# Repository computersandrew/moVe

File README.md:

# moVe

High-performance (ish) STM32H7 sensor suite and navigation platform for autonomous drones, planes, cars, and boats. Featuring ICM-20948, BMP390, u-blox M10 GNSS, u-blox NORA-B261 Bluetooth LE, and an RGB TFT cockpit display path. Will include non-volatile storage for datalogging, map/chart assets, and USB.

PCB Hardware Design and Implementation done using Ki-Cad

3D Design and Modeling done using Siemens NX

Prototyping & Manufacturing done at Rensselaer Polytechnic Institute

To include a header for possible 3.3V LiPo Cells

PCA9306 Level Shifter(s)

This is a plain C STM32 HAL implementation for:

## Custom Board

- Main MCU: STM32H723ZGT6.
- STM32H723ZG datasheet: [STMicroelectronics PDF](https://www.st.com/resource/en/datasheet/stm32h723zg.pdf).
- Designed as a custom single board in KiCad.
- Pinout: `docs/pinout.md`.
- KiCad test platform PCB: `hardware/moVe_test/` (schematic, routed 4-layer board, images).
- u-blox NORA-B261 Bluetooth LE module on a UART host link, with reset/recovery/test lines reserved.
- Display direction: Newhaven `NHD-5.0-800480TF-ATXL-CTP`, driven with LTDC RGB, DMA2D, and external SDRAM.
- Storage direction: `SDMMC2` microSD in 4-bit mode for logs and chart/map tiles.

## Test Platform PCB (KiCad)

A round **4.2 in (106.68 mm), 4-layer** bring-up board that carries every subsystem below lives in
[`hardware/moVe_test/`](hardware/moVe_test/) — full KiCad project, schematic PDF, layer images and design notes.

- **Fully routed:** 521/521 connections, DRC 0 errors, 146 parts.
- **Stackup:** signal / solid GND / +3V3 plane / signal (1.6 mm).
- **Schematic:** 7 sheets (Power, MCU, Memory, Display, Sensors, Radio, CO sensor), each organized into titled functional blocks — [PDF](hardware/moVe_test/moVe_test_schematic.pdf).
- **Pin assignments:** previously TBD pins are now assigned in [`docs/pinout.md`](docs/pinout.md).
- **Cost:** about $142 per board ($77 components + $64 display + PCB), with a priced BOM in [`bom/moVe_test_BOM.csv`](hardware/moVe_test/bom/moVe_test_BOM.csv).

See [`hardware/moVe_test/README.md`](hardware/moVe_test/README.md) for all layers, every schematic sheet, the
stackup rationale, design notes and how to regenerate the files.

## ICM-20948 + Madgwick AHRS for STM32H7
[Datasheet](https://d17t6iyxenbwp1.cloudfront.net/s3fs-public/2026-01/DS-000189-ICM-20948-v1.6.pdf?VersionId=XteIUeEiGGKWJDQjSzr3D2K3OIitFvHY)

- To run on 1.8V Bus - Low-Dropout Regulator (MIC5225)
- ICM-20948 by InvenSense TDK
- ICM-20948 accelerometer and gyroscope over I2C. 
- ICM-20948 contains the AK09916 magnetometer (allegedly according to adafruit) through ICM-20948 bypass mode.
- Madgwick 6-axis or 9-axis attitude filtering.
- Roll, pitch, yaw, and aircraft/drone display ready instrument values.
- Roll/Pitch applications for marine use

## BMP390 + Simple Kalman Filtering for STM32H7
[Datasheet](https://www.mouser.com/datasheet/3/1046/1/bst_bmp390_ds002.pdf)
- To run on 3.3V Bus
- BMP390 by Bosch 
- I2C, SPI capabilities
- Also, temperature capabilities 
- Compensated pressure and temperature over I2C.
- Pressure altitude conversion with configurable sea-level pressure.
- Two-state Kalman filter for altitude and vertical speed.

## U-Blox MAX-M10S for STM32H7

[Datasheet](https://content.u-blox.com/sites/default/files/MAX-M10S_DataSheet_UBX-20035208.pdf)
- To run on 3.3V Bus
- moving map/navigation
- Outputs MSL elevation data, Ground Speed, Lat/Long Coordinates
- Will include uFL connector, as well as ceramic patch antenna by default
- Parses both UBX binary navigation messages and NMEA sentences.
- GPS ground speed feeds the airspeed display as a fallback speed source.

## u-blox NORA-B261 Bluetooth LE Module
[Datasheet](https://content.u-blox.com/sites/default/files/documents/NORA-B26_DataSheet_UBXDOC-465451970-4608.pdf)

- To run on 3.3V bus.
- NORA-B261 uses u-connectXpress firmware with an AT-command host interface.
- Host interface starts as asynchronous UART from STM32H723ZGT6 to NORA-B261.
- Optional RTS/CTS hardware flow control should be reserved in the schematic.
- Include NORA reset, recovery/test access, and optional IRQ/attention GPIOs.
- The B261 variant uses an antenna pin, so route a 50 ohm 2.4 GHz RF path to a chip antenna or u.FL.

## Graphical Display Path
[Datasheet](https://newhavendisplay.com/content/specs/NHD-5.0-800480TF-ATXL-CTP.pdf)

- Newhaven `NHD-5.0-800480TF-ATXL-CTP` 5 inch, 800x480 RGB TFT with capacitive touch.
- STM32 `LTDC` drives the parallel RGB display interface.
- STM32 `DMA2D` accelerates fills, blits, and pixel format conversion.
- External SDRAM on `FMC SDRAM 1` holds the framebuffer; start with a 16-bit SDRAM bus.
- Use `RGB565` for the first framebuffer format even though the physical panel interface is RGB888.
- Touch uses I2C plus touch interrupt/reset GPIOs.
- Backlight needs a separate LED boost/current driver, not a direct STM32 GPIO.
- FAA sectionals/charts should be preprocessed into raster tiles and loaded from SD instead of rendering full PDFs on the MCU.
- Moving-map firmware maps current GNSS position to predownloaded XYZ raster tiles and can stream the current tile state over the NORA-B261 link.
- Google Maps tiles should only be used through a licensed/offline workflow that permits embedded use; the firmware tile math is provider-neutral.

## Aircraft Carbon Monoxide Sensor

- Aircraft-only MQ-7/MQ-7B carbon monoxide sensor direction.
- Firmware exposes alert triggers at 25 ppm, 50 ppm, and 100 ppm.
- MQ-7 heater cycling is modeled as a high-temperature clean phase and low-temperature measurement phase.
- Real CO ppm readings require analog calibration, heater driver hardware, and validation before any aircraft safety use.

## Parts List

- GitHub spreadsheet/BOM: `docs/parts.csv`
- STM32H723ZGT6 MCU
- u-blox NORA-B261 Bluetooth LE module
- U-Blox MAX-M10S GNSS receiver
- ICM-20948 9-axis IMU
- BMP390 pressure/temperature sensor
- Aircraft-only MQ-7/MQ-7B carbon monoxide sensor
- Newhaven `NHD-5.0-800480TF-ATXL-CTP` RGB TFT with capacitive touch
- 16-bit external SDRAM for framebuffer storage
- Backlight LED boost/current driver for the TFT
- PCA9306 level shifter(s), if mixed-voltage I2C is kept
- MIC5225 or equivalent low-noise LDO for 1.8 V rail
- 3.3 V regulator sized for STM32, GNSS, NORA-B261, SD, and display
- USB-C Connector (5V 500mA)
- SD card socket
- Optional battery connector and protected 2-cell input path
- ADC battery-sense divider and optional current-sense amplifier
- GNSS antenna path: u.FL and/or ceramic patch antenna
- NORA-B261 antenna path: chip antenna or u.FL with matching network
- STM32 SWD header
- NORA-B261 reset/recovery test pads
- Reset and boot buttons or test pads

## Files (so far) will update

- `Core/Inc/icm20948.h`
- `Core/Src/icm20948.c`
- `Core/Inc/madgwick.h`
- `Core/Src/madgwick.c`
- `Core/Inc/icm20948_madgwick_example.h`
- `Core/Src/icm20948_madgwick_example.c`
- `Core/Inc/navigation_fusion.h`
- `Core/Src/navigation_fusion.c`
- `Core/Inc/moving_map.h`
- `Core/Src/moving_map.c`
- `Core/Inc/nora_b261.h`
- `Core/Src/nora_b261.c`
- `Core/Src/main.c`
- `moVe.ioc`
- `docs/pinout.md`
- `docs/parts.csv`
- `Core/Inc/bmp390.h`
- `Core/Src/bmp390.c`
- `Core/Inc/kalman_altitude.h`
- `Core/Src/kalman_altitude.c`
- `Core/Inc/max_m10s.h`
- `Core/Src/max_m10s.c`
- `Aircraft/Inc/aircraft_instruments.h`
- `Aircraft/Src/aircraft_instruments.c`
- `Aircraft/Inc/attitude_indicator.h`
- `Aircraft/Src/attitude_indicator.c`
- `Aircraft/Inc/turn_slip.h`
- `Aircraft/Src/turn_slip.c`
- `Aircraft/Inc/heading_indicator.h`
- `Aircraft/Src/heading_indicator.c`
- `Aircraft/Inc/altimeter.h`
- `Aircraft/Src/altimeter.c`
- `Aircraft/Inc/airspeed_indicator.h`
- `Aircraft/Src/airspeed_indicator.c`
- `Aircraft/Inc/g_meter.h`
- `Aircraft/Src/g_meter.c`
- `Aircraft/Inc/mq7_co.h`
- `Aircraft/Src/mq7_co.c`
- `Aircraft/Inc/vertical_speed_indicator.h`
- `Aircraft/Src/vertical_speed_indicator.c`
- `Aircraft/Inc/aircraft_math.h`
- `Aircraft/Src/aircraft_math.c`
- `Crew/Inc/crew_instruments.h`
- `Crew/Src/crew_instruments.c`

## Aircraft Display Outputs

- Converts the same IMU, GPS, and BMP390 data path into aircraft-facing instrument values.
- Attitude reports roll and pitch from filtered AHRS output.
- Turn-and-slip reports yaw-rate turn indication and lateral-acceleration slip ball.
- Heading reports display heading with configurable magnetic declination.
- Altimeter and VSI report altitude and vertical speed from BMP390 pressure and the altitude filter.
- Airspeed reports estimated true airspeed from GNSS speed plus pressure/temperature, with GPS ground-speed fallback.
- G-meter reports smoothed normal acceleration plus positive and negative peak G values.

## Crew Display Outputs

- Converts the same IMU, GPS, and BMP390 data path into rowing-facing values.
- Roll state reports `Port`, `Starboard`, or `Set` from filtered roll angle.
- Speed uses GNSS ground speed when valid and exposes meters/second, km/h, and knots.
- Stroke rate estimates strokes per minute from cyclic IMU acceleration.
- Stroke phase reports `Catch`, `Drive`, or `Recovery` with phase and cycle timing.
- Temperature comes from the BMP390 compensated temperature sample.

## STM32CubeIDE Use

Copy the `Core/Inc`, `Core/Src`, `Aircraft/Inc`, `Aircraft/Src`, `Crew/Inc`, and `Crew/Src` files into your STM32H7 project. Enable I2C in CubeMX, then make sure the example uses the matching handle:

```c
extern I2C_HandleTypeDef hi2c1;
```

The Cube-style entry point is `Core/Src/main.c`. It shows the expected HAL init order for the H723 board direction, including I2C sensors, GPS UART, NORA-B261 UART, ADC battery sense, CRC, FMC SDRAM, DMA2D, LTDC, SDMMC2, USB OTG HS device mode with internal FS PHY, GPS UART byte reception, and the navigation fusion update loop.

Legacy compatibility wrappers are still available. Call this once after `MX_I2C1_Init()`:

```c
Attitude_Init();
```

Call this repeatedly from your main loop or a fixed-rate task:

```c
Attitude_Update();
```

The latest Euler angles are in:

```c
#include "icm20948_madgwick_example.h"

attitude_deg.roll_deg;
attitude_deg.pitch_deg;
attitude_deg.yaw_deg;
```

The moving-map tile state is in:

```c
#include "navigation_fusion.h"

const MovingMapState *map_state =
    NavigationFusion_GetMovingMapState(&navigation_fusion);

char nora_frame[160];
NavigationFusion_BuildNoraB261MovingMapFrame(&navigation_fusion,
                                             "maps/faa",
                                             "tile",
                                             nora_frame,
                                             sizeof(nora_frame));
```

The display-ready aircraft instrument values are in:

```c
#include "icm20948_madgwick_example.h"

aircraft_display->attitude.roll_deg;
aircraft_display->attitude.pitch_deg;
aircraft_display->turn_slip.turn_rate_deg_s;
aircraft_display->turn_slip.standard_rate_fraction;
aircraft_display->turn_slip.slip_ball;
aircraft_display->heading.display_heading_deg;
aircraft_display->altimeter.display_altitude_ft;
aircraft_display->vsi.vertical_speed_fpm;
aircraft_display->airspeed.display_true_airspeed_kt;
aircraft_display->g_meter.normal_g;
aircraft_display->g_meter.peak_positive_g;
aircraft_display->g_meter.peak_negative_g;
AircraftInstruments_ResetGMeterPeaks(&aircraft_instruments);
```

The crew display values are in:

```c
#include "icm20948_madgwick_example.h"

crew_display->roll_deg;
CrewInstruments_RollStateText(crew_display->roll_state);
crew_display->speed_mps;
crew_display->speed_kph;
crew_display->speed_kt;
crew_display->strokes_per_minute;
CrewInstruments_StrokePhaseText(crew_display->stroke_phase);
crew_display->current_phase_time_s;
crew_display->catch_time_s;
crew_display->drive_time_s;
crew_display->recovery_time_s;
crew_display->drive_recovery_ratio;
crew_display->recovery_drive_ratio;
crew_display->stroke_cycle_time_s;
crew_display->temperature_c;
```

The aircraft display layer is split by instrument. `Aircraft/Src/aircraft_instruments.c` coordinates the attitude indicator, turn-and-slip, heading card, altimeter, VSI, and airspeed modules without owning their display math.
The crew display layer is in `Crew/Src/crew_instruments.c` and is updated by `NavigationFusion_Update()` alongside the aircraft outputs.

## Notes

- Gyro values are converted from degrees/second to radians/second before entering Madgwick.
- The driver configures accel at +/-16 g and gyro at +/-2000 dps.
- The magnetometer is read at 100 Hz. If no new magnetometer data is ready, the filter falls back to the IMU-only Madgwick update for that frame.
- Real yaw quality depends heavily on magnetometer hard-iron and soft-iron calibration. Use `ICM20948_SetMagCalibration()` after you measure your board's calibration values.
- If yaw moves the wrong way, align the AK09916 axes to the accel/gyro frame with `ICM20948_SetMagAxisTransform()`.
- Set local magnetic declination with `AircraftInstruments_SetDeclination()` if the heading display should show true heading instead of magnetic heading.
- Set local altimeter pressure with `BMP390_SetSeaLevelPressure()` before converting pressure to altitude.
- The airspeed indicator displays estimated true airspeed when it has GPS speed plus BMP390 static pressure and temperature. If temperature or pressure are unavailable, it falls back to pressure-altitude ISA correction, then GPS ground speed.
- Aircraft use needs independent validation, redundancy, failure annunciation, and compliance work before it can be trusted as flight-critical instrumentation.
- If AD0 is high on your board, initialize with `ICM20948_ADDR_AD0_HIGH` instead of `ICM20948_ADDR_AD0_LOW`.
- Link with the math library if your toolchain requires it, usually by adding `-lm`.

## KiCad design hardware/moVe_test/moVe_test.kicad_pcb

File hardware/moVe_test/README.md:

# moVe test platform — KiCad hardware (rev A)

A round **4.2 in (106.68 mm)**, **4-layer** bring-up board for the moVe STM32H723ZGT6 platform. It carries every
subsystem from the main README: SDRAM framebuffer, RGB TFT + capacitive touch, microSD, ICM-20948, BMP390,
MAX-M10S GNSS, NORA-B261 Bluetooth LE, the aircraft MQ-7 CO sensor, USB-C and a 2S battery input.

* Schematic: [`moVe_test_schematic.pdf`](moVe_test_schematic.pdf) (8 pages) · KiCad project: [`moVe_test.kicad_pro`](moVe_test.kicad_pro)
* Status: **fully routed — 521/521 connections, DRC 0 errors, 0 unconnected**, 146 parts
* Format: KiCad 7 (KiCad 8/9 open it and offer to upgrade)

<p align="center"><em>Top side (left) and bottom side, mirrored (right).</em></p>

---

## Layer stackup — 4 layers

| Layer | Use |
|---|---|
| L1 `F.Cu` | Signals + components, GND pour |
| L2 `In1.Cu` | Solid GND plane |
| L3 `In2.Cu` | Solid +3V3 plane |
| L4 `B.Cu` | Signals + MCU/SDRAM decoupling, GND pour |

1.6 mm board (e.g. JLC04161H-7628). Rules: 0.15 mm track / 0.127 mm clearance, 0.6/0.3 mm vias, power 0.5 mm,
RF 0.36 mm (≈50 Ω microstrip over L2 with 7628 prepreg — confirm with your fab's impedance calculator).

**Why 4 layers:** 2 layers can't give the ~100 MHz SDRAM bus, the 24-bit LTDC bus, USB and the two 50 Ω RF feeds an
unbroken reference plane. The routed result confirms 4 is enough: every signal fits on L1/L4 with L2/L3 left as
solid planes (521 connections, 498 vias, ~7.1 m of copper). 6 layers is the upgrade path only if you want the SDRAM
bus length-matched on an inner stripline layer.

<table>
  <tr>
    <td></td>
    <td></td>
  </tr>
  <tr>
    <td></td>
    <td></td>
  </tr>
  <tr>
    <td></td>
    <td></td>
  </tr>
</table>

Both copper layers together (red = top, blue = bottom):

---

## Schematic

Each sheet is organized into titled functional blocks: supply arrows point up and GND down, same-net power
pins are bussed, net names sit on wires for sheet-local nets, and global flag labels mark nets shared between
sheets. Text placement is collision-checked, so no text overlaps.

| Sheet | Blocks |
|---|---|
| [Power](images/sch_2_power.png) | USB-C input, power path (USB / 2S battery), 3.3 V and 1.8 V regulators, voltage sense, power LED, test points, mounting holes |
| [MCU](images/sch_3_mcu.png) | STM32H723ZGT6, supply decoupling, 25 MHz / 32.768 kHz clocks, reset and boot, SWD, status LEDs, expansion header |
| [Memory](images/sch_4_memory.png) | SDRAM framebuffer, microSD (SDMMC2) |
| [Display](images/sch_5_display.png) | 40-pin RGB TFT connector, capacitive touch, TPS61165 backlight driver |
| [Sensors](images/sch_6_sensors.png) | ICM-20948 (1.8 V), BMP390, PCA9306 I2C level shift, IMU INT level shift |
| [Radio](images/sch_7_radio.png) | MAX-M10S GNSS, NORA-B261 Bluetooth LE |
| [CO sensor](images/sch_8_co_sensor.png) | MQ-7 heater and sense (aircraft build) |

<details open><summary><b>Power</b></summary></details>
<details><summary><b>MCU</b></summary></details>
<details><summary><b>Memory</b></summary></details>
<details><summary><b>Display</b></summary></details>
<details><summary><b>Sensors</b></summary></details>
<details><summary><b>Radio</b></summary></details>
<details><summary><b>CO sensor</b></summary></details>

For full resolution open the [PDF](moVe_test_schematic.pdf) or the project in KiCad.

---

## Pin assignments added for this board

These were TBD in [`docs/pinout.md`](../../docs/pinout.md) (now updated). Mirror them in `moVe.ioc` (CubeMX) before
generating firmware.

| Signal | STM32 pin | Notes |
|---|---|---|
| BLE_CTS / BLE_RTS | PD11 / PD12 | USART3 CTS/RTS (AF7). MCU RTS → NORA CTS (F9), NORA RTS (F8) → MCU CTS |
| BLE_RESET_N, BLE_SW1, BLE_SW2 | PD13, PD4, PD5 | NORA J3, D8, C8 |
| BLE_WAKE | PC12 | NORA J9; shared with expansion header pin 7 |
| GPS_RESET_N, GPS_EXTINT, GPS_TIMEPULSE | PG3, PG14, PE2 | TIMEPULSE on EXTI2 |
| IMU_INT, BARO_INT, TOUCH_INT_N, SD_DETECT | PE3, PB4, PC13, PC8 | separate EXTI lines 3 / 4 / 13 / 8 |
| TOUCH_RST_N, LCD_STBYB | PB12, PB13 | STBYB has a 10k pull-down (panel in standby until firmware enables it) |
| BL_PWM, MQ7_HEAT | PB8 (TIM16_CH1), PB9 (TIM17_CH1) | independent timers |
| MQ7_ADC, VBAT_SENSE, VBUS_SENSE | PC5 (ADC12_INP8), PC4, PA9 | VBUS 10k/20k; VBAT 100k/33k (8.4 V → 2.08 V) |
| LED1, LED2 | PF6, PF7 | |
| SWO | PB3 | 10-pin Cortex SWD header |
| Expansion header J2 | — | 3V3, GND, SCL, SDA, PF8, PF9, PC12/BLE_WAKE, VSYS |

PD7 and PB2 are left unused.

## Bill of materials and cost

Full BOM with quantities, MPNs, unit prices and DigiKey links: [`bom/moVe_test_BOM.csv`](bom/moVe_test_BOM.csv) (61 lines, 130 fitted parts).

| | Per board (USD) |
|---|---|
| Components (excluding display) | $76.57 |
| Display — NHD-5.0-800480TF-ATXL-CTP (off-board) | $63.83 |
| PCB fabrication, 4-layer (estimate) | $2.00 |
| **Total** | **$142.40** |

About $712 for a 5-board build. Prices are quantity-1, USD, without shipping or tariffs, as of Nov 2026.

* Most ICs and connectors come from the April 2026 prices in [`docs/parts.csv`](../../docs/parts.csv); the rest are distributor prices from Nov 2026 (the source is in the `Price basis` column).
* Passives, LEDs, the small MOSFETs and diodes, and the 1x8 header are estimates assuming 10+ cut-tape quantities. At single-piece prices (~$0.10 each) they add about $8 per board.
* For the generic passives, the link is a DigiKey search by value and package; choose a specific part before ordering.
* PCB cost is a placeholder; get a real quote by uploading the Gerbers.
* The display spec calls out a Molex FPC connector; J6 is a Hirose FH12-40S. Check the contact side before ordering.

## Design notes worth checking

* **Power:** USB-C VBUS → 1.1 A PTC → `+5V` (MQ-7 heater) → SS34 → `VSYS`; 2S battery (JST-PH) → SS34 → `VSYS`.
  VSYS → TLV1117-33 → +3V3 → AP2112K-1.8 → +1V8. At 8.4 V battery input the TLV1117 dissipates ~1.5 W; consider a buck converter for battery use.
* **MCU:** 25 MHz HSE crystal placed beside PH0/PH1 (both lines < 8 mm, no vias), 32.768 kHz LSE, VCAP pins tied with
  2 × 2.2 µF, VDDA/VREF+ behind a ferrite. Firmware must use `PWR_LDO_SUPPLY` (the H723ZG has no SMPS).
* **ICM-20948:** VDD and VDDIO on 1.8 V behind a PCA9306; INT level-shifted to 3.3 V with a BSS138.
  **AD0 is tied high → I2C address 0x69** — initialise with `ICM20948_ADDR_AD0_HIGH`.
* **SDRAM:** the symbol is MT48LC16M16A2P so FMC_A12 (PG2) reaches pin 36. The AS4C4M16SA is fitted (pin 36 = NC);
  the Micron 32 MB part drops in.
* **NORA-B261:** footprint follows data-sheet Fig. 5. Fig. 2 also shows GND pads K3/K7 that Fig. 5 omits; they're
  left out — verify. ANT → 0R + two DNP 0402 shunts (pi match) → u.FL.
* **MAX-M10S:** u.FL only (passive antenna, no VCC_RF bias); VIO_SEL open; SAFEBOOT_N on a test pad.
* **MQ-7:** AO3400A low-side heater switch, 10k load resistor, 10k/20k divider into the ADC.
* **Display connectors:** Hirose FH12-40S-0.5SH footprint for the 40-pin FPC (Newhaven lists Molex 54104-4031 —
  check the contact side before ordering) and Molex 200528-0060 for the 6-pin touch FFC. Backlight: TPS61165 with
  6.8 Ω sense ≈ 29 mA.

## Verification

* Schematic netlist ↔ `generator/design.py`: 0 mismatches. PCB pad nets ↔ schematic: 0 mismatches.
* DRC: 0 errors, 0 unconnected. The 20 remaining `lib_footprint_mismatch` warnings come from moving 50 overlapping
  silkscreen outline segments to the Fab layer; **don't run "Update footprints from library"** on those parts or the
  overlaps come back.
* Silkscreen: 0 overlaps, 0 silk-over-pad; all references visible.
* ERC has not been run (KiCad 7's command line has no ERC) — run Inspect → ERC in KiCad.

**Before fab:** routes are autorouted, not length-matched — FMC nets run 15–88 mm (SDCLK 45 mm), fine for bring-up at
≤ 100 MHz. USB D+/D− are routed separately (OK for 12 Mb/s full-speed). VBUS at the USB-C pins uses 0.3 mm traces
(the USB4105 pads are too small for 0.5 mm); the run is short and fine for 1 A.

## Regenerating

Everything is generated from [`generator/design.py`](generator/design.py) (one netlist definition drives the
schematic and the board) with the KiCad 7 Python API (`pcbnew`):

```sh
cd hardware/moVe_test/generator
python3 gen_sch.py              # schematic sheets, project symbol/footprint libraries
kicad-cli sch export netlist -o ../moVe_test.net ../moVe_test.kicad_sch
python3 check_net.py ../moVe_test.net   # netlist must match design.py
```

The board was placed with `gen_pcb.py`, fanned out with `fanout.py`, autorouted with
[Freerouting](https://github.com/freerouting/freerouting) (`prep_route.py`, `import_ses.py`), then finished with
`ripup_route.py` and `silk_fix.py`. Set `KICAD7_SYMBOL_DIR`, `KICAD7_FOOTPRINT_DIR` and `FREEROUTING_JAR` if your
KiCad libraries or the Freerouting jar aren't in the Linux default locations. Re-running placement discards the
current routing.

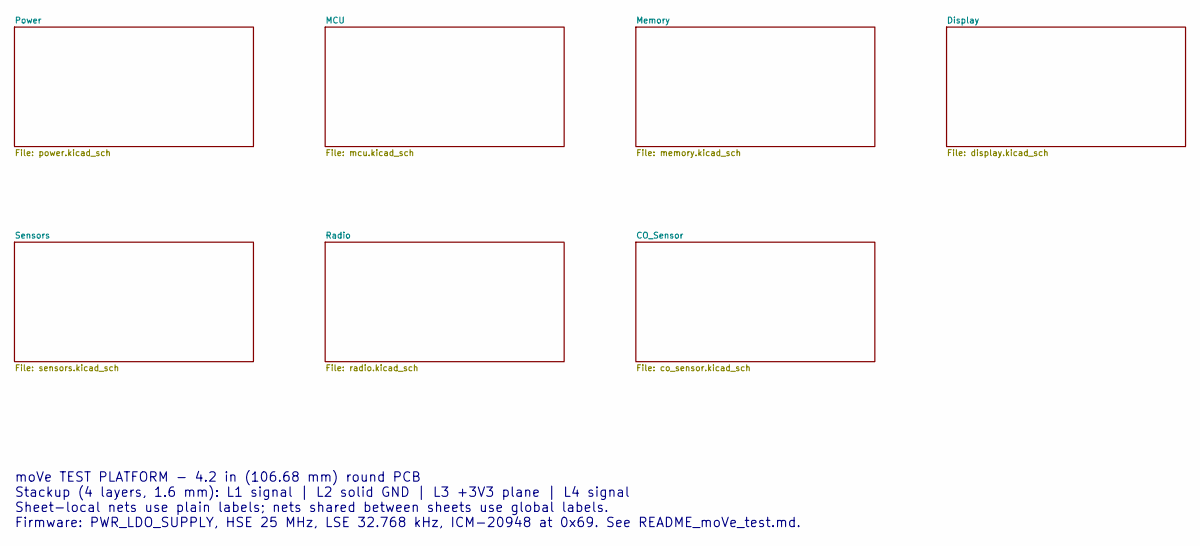
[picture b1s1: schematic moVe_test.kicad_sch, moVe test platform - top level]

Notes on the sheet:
moVe TEST PLATFORM - 4.2 in (106.68 mm) round PCB Stackup (4 layers, 1.6 mm): L1 signal | L2 solid GND | L3 +3V3 plane | L4 signal Sheet-local nets use plain labels; nets shared between sheets use global labels. Firmware: PWR_LDO_SUPPLY, HSE 25 MHz, LSE 32.768 kHz, ICM-20948 at 0x69. See README_moV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

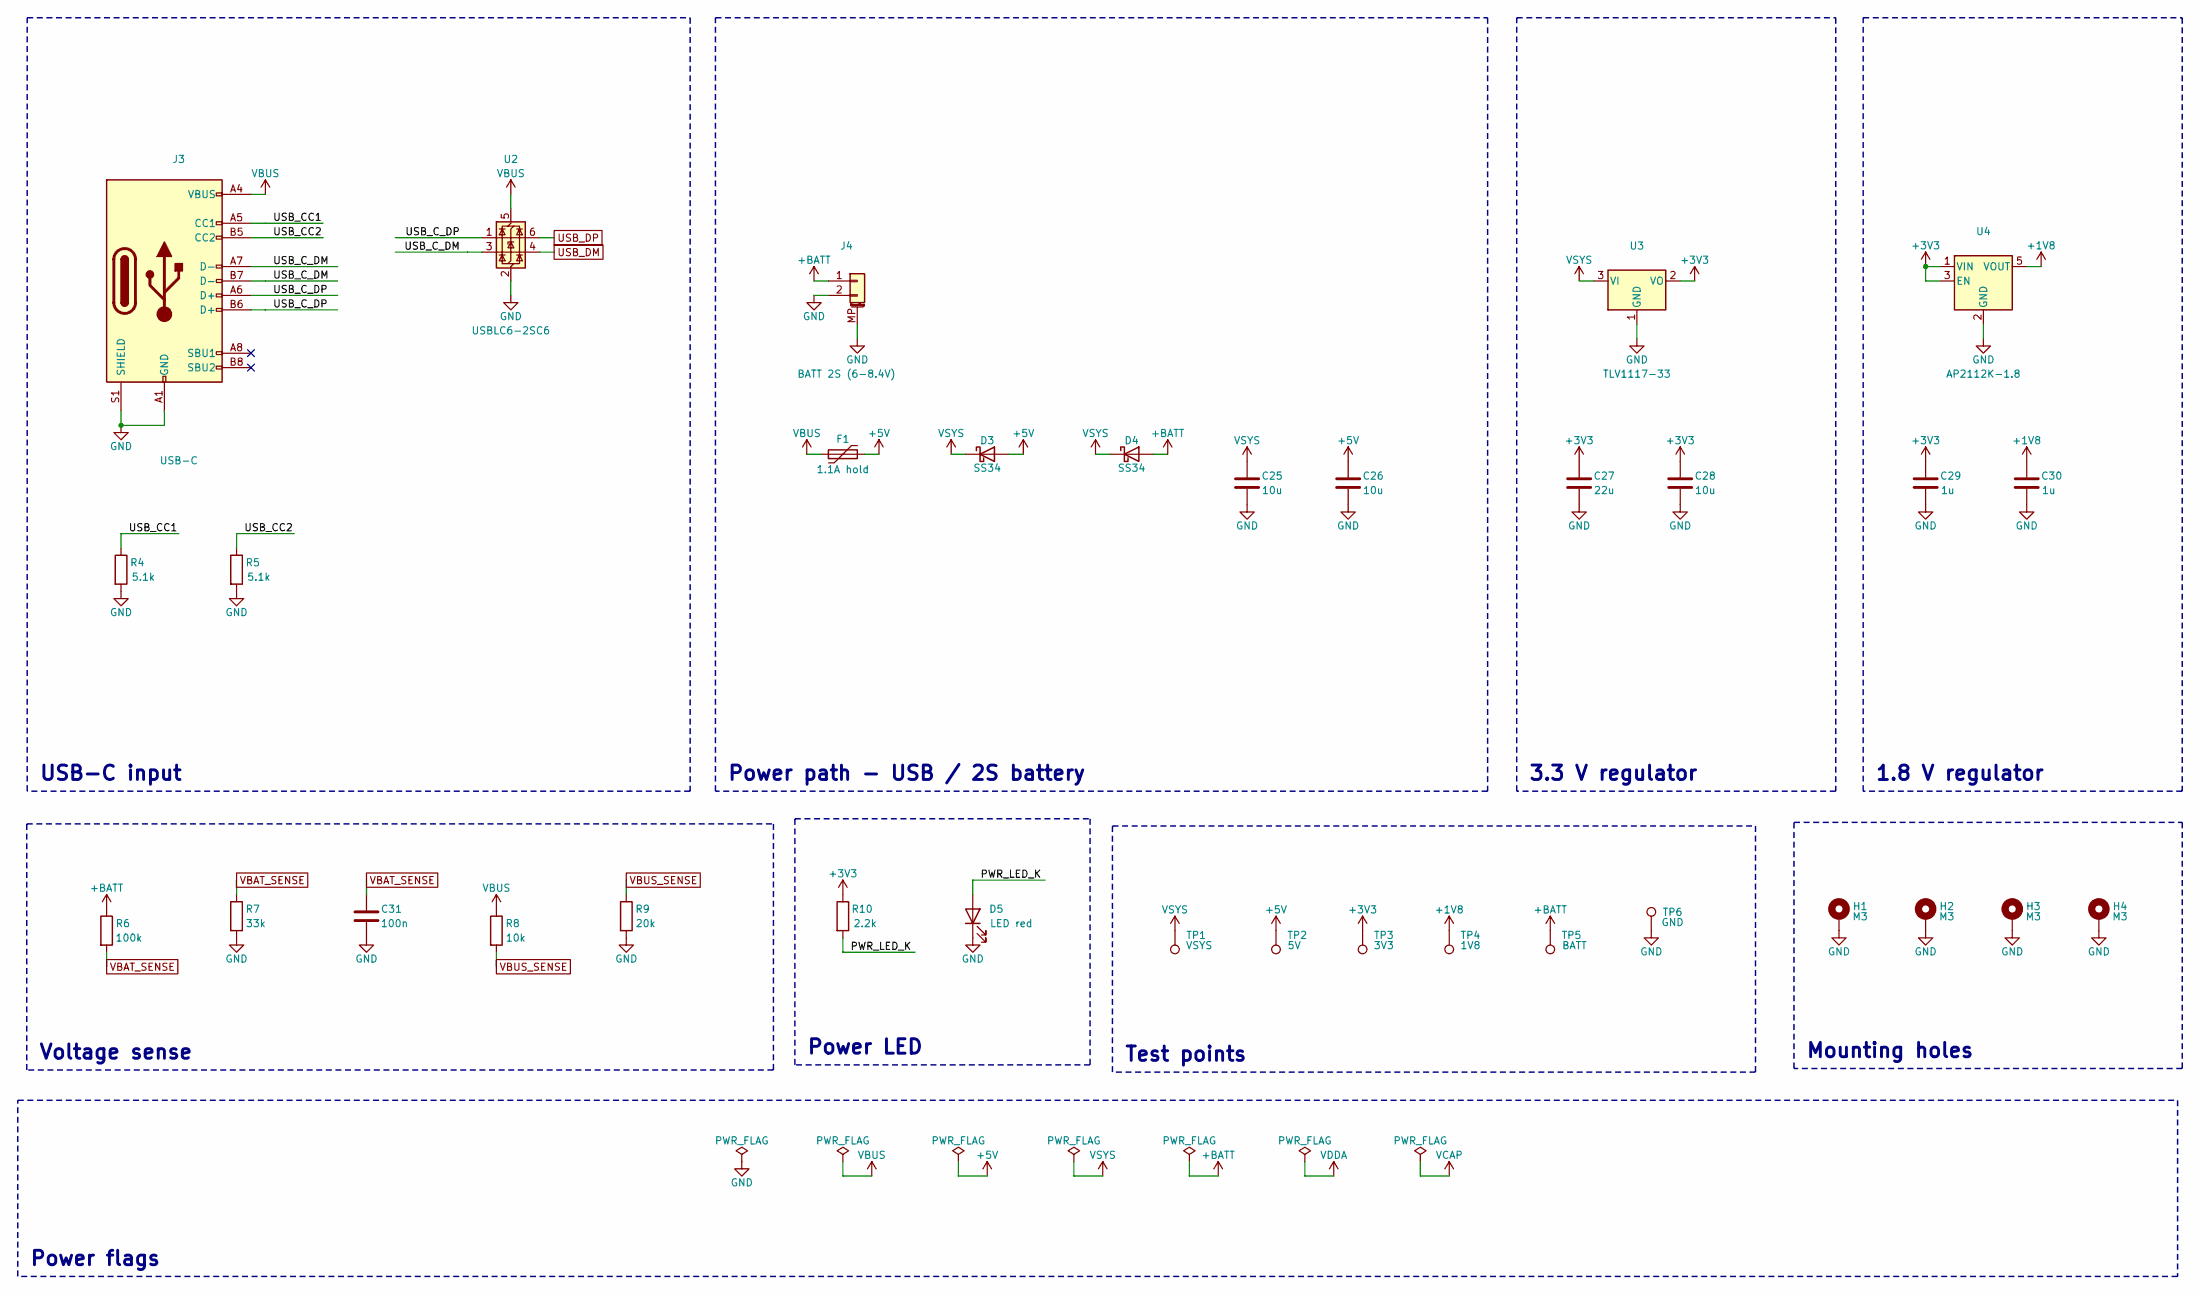
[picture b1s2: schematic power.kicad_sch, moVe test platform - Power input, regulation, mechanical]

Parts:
C25: 10u; C_1206_3216Metric
C26, C28: 10u; C_0805_2012Metric
C27: 22u; C_1206_3216Metric
C29, C30: 1u; C_0603_1608Metric
C31: 100n; C_0603_1608Metric
D3, D4: SS34; D_SMA; MPN SS34
D5: LED red; LED_0603_1608Metric
F1: 1.1A hold; Fuse_1206_3216Metric; MPN Bourns MF-MSMF110-2
H1, H2, H3, H4: M3; MountingHole_3.2mm_M3_Pad_Via
J3: USB-C; USB_C_Receptacle_GCT_USB4105-xx-A_16P_TopMnt_Horizontal; MPN USB4105-GF-A-120
J4: BATT 2S (6-8.4V); JST_PH_B2B-PH-SM4-TB_1x02-1MP_P2.00mm_Vertical; MPN B2B-PH-SM4-TB(LF)(SN)
R4, R5: 5.1k; R_0603_1608Metric
R6: 100k; R_0603_1608Metric
R7: 33k; R_0603_1608Metric
R8: 10k; R_0603_1608Metric
R9: 20k; R_0603_1608Metric
R10: 2.2k; R_0603_1608Metric
TP1: VSYS; TestPoint_Pad_D1.5mm
TP2: 5V; TestPoint_Pad_D1.5mm
TP3: 3V3; TestPoint_Pad_D1.5mm
TP4: 1V8; TestPoint_Pad_D1.5mm
TP5: BATT; TestPoint_Pad_D1.5mm
TP6: GND; TestPoint_Pad_D1.5mm
U2: USBLC6-2SC6; SOT-23-6; MPN USBLC6-2SC6
U3: TLV1117-33; TO-252-3_TabPin2; MPN TLV1117-33IKVURG3
U4: AP2112K-1.8; SOT-23-5; MPN AP2112K-1.8TRG1

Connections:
+1V8: C30.1, TP4.1, U4.5 (VOUT); also elsewhere on the board
+3V3: C27.1, C28.1, C29.1, R10.1, TP3.1, U3.2 (VO), U4.1 (VIN), U4.3 (EN); also elsewhere on the board
+5V: C26.1, D3.2 (A), F1.2, TP2.1; also elsewhere on the board
+BATT: D4.2 (A), J4.1, R6.1, TP5.1
/Power/PWR_LED_K: D5.2 (A), R10.2
/Power/USB_CC1: J3.A5 (CC1), R4.1
/Power/USB_CC2: J3.B5 (CC2), R5.1
/Power/USB_C_DM: J3.A7 (D-), J3.B7 (D-), U2.3 (I/O2)
/Power/USB_C_DP: J3.A6 (D+), J3.B6 (D+), U2.1 (I/O1)
GND: C25.2, C26.2, C27.2, C28.2, C29.2, C30.2, C31.2, D5.1 (K), H1.1, H2.1, H3.1, H4.1, J3.A1 (GND), J3.A12 (GND), J3.B1 (GND), J3.B12 (GND), J3.S1 (SHIELD), J4.2, J4.MP (MountPin), R4.2, R5.2, R7.2, R9.2, TP6.1, U2.2 (GND), U3.1 (GND), U4.2 (GND); also elsewhere on the board
USB_DM: U2.4 (I/O2); also elsewhere on the board
USB_DP: U2.6 (I/O1); also elsewhere on the board
VBAT_SENSE: C31.1, R6.2, R7.1; also elsewhere on the board
VBUS: F1.1, J3.A4 (VBUS), J3.A9 (VBUS), J3.B4 (VBUS), J3.B9 (VBUS), R8.1, U2.5 (VBUS)
VBUS_SENSE: R8.2, R9.1; also elsewhere on the board
VSYS: C25.1, D3.1 (K), D4.1 (K), TP1.1, U3.3 (VI); also elsewhere on the board

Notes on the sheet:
USB-C input
Power path - USB / 2S battery
3.3 V regulator
1.8 V regulator
Voltage sense
Power LED
Test points
Mounting holes
Power flags

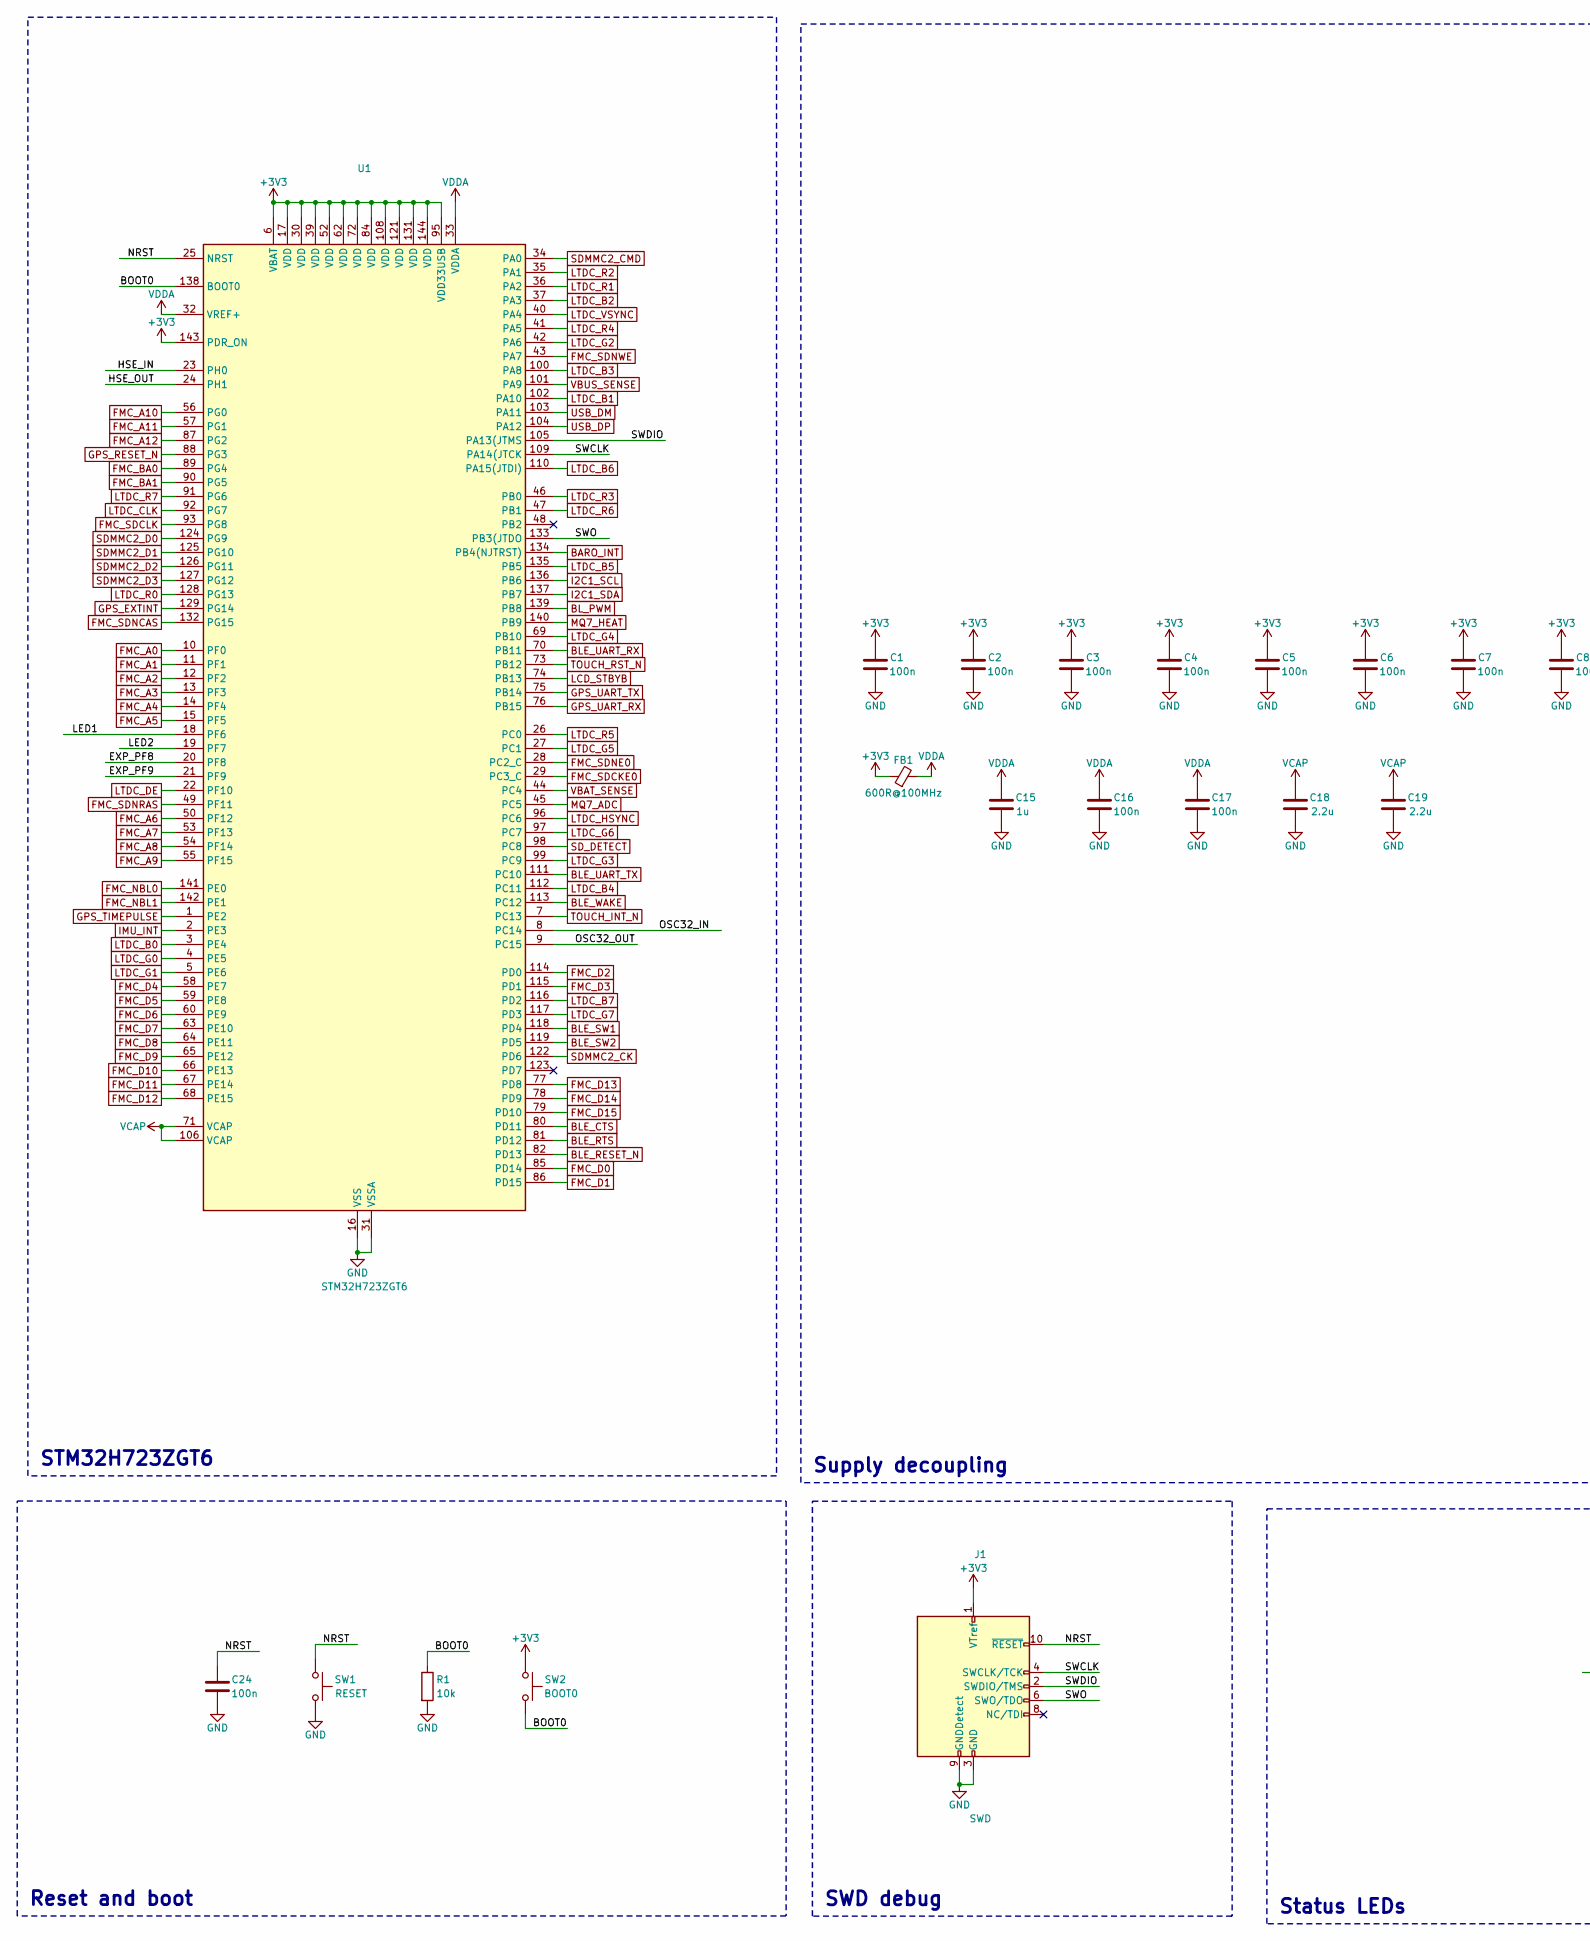
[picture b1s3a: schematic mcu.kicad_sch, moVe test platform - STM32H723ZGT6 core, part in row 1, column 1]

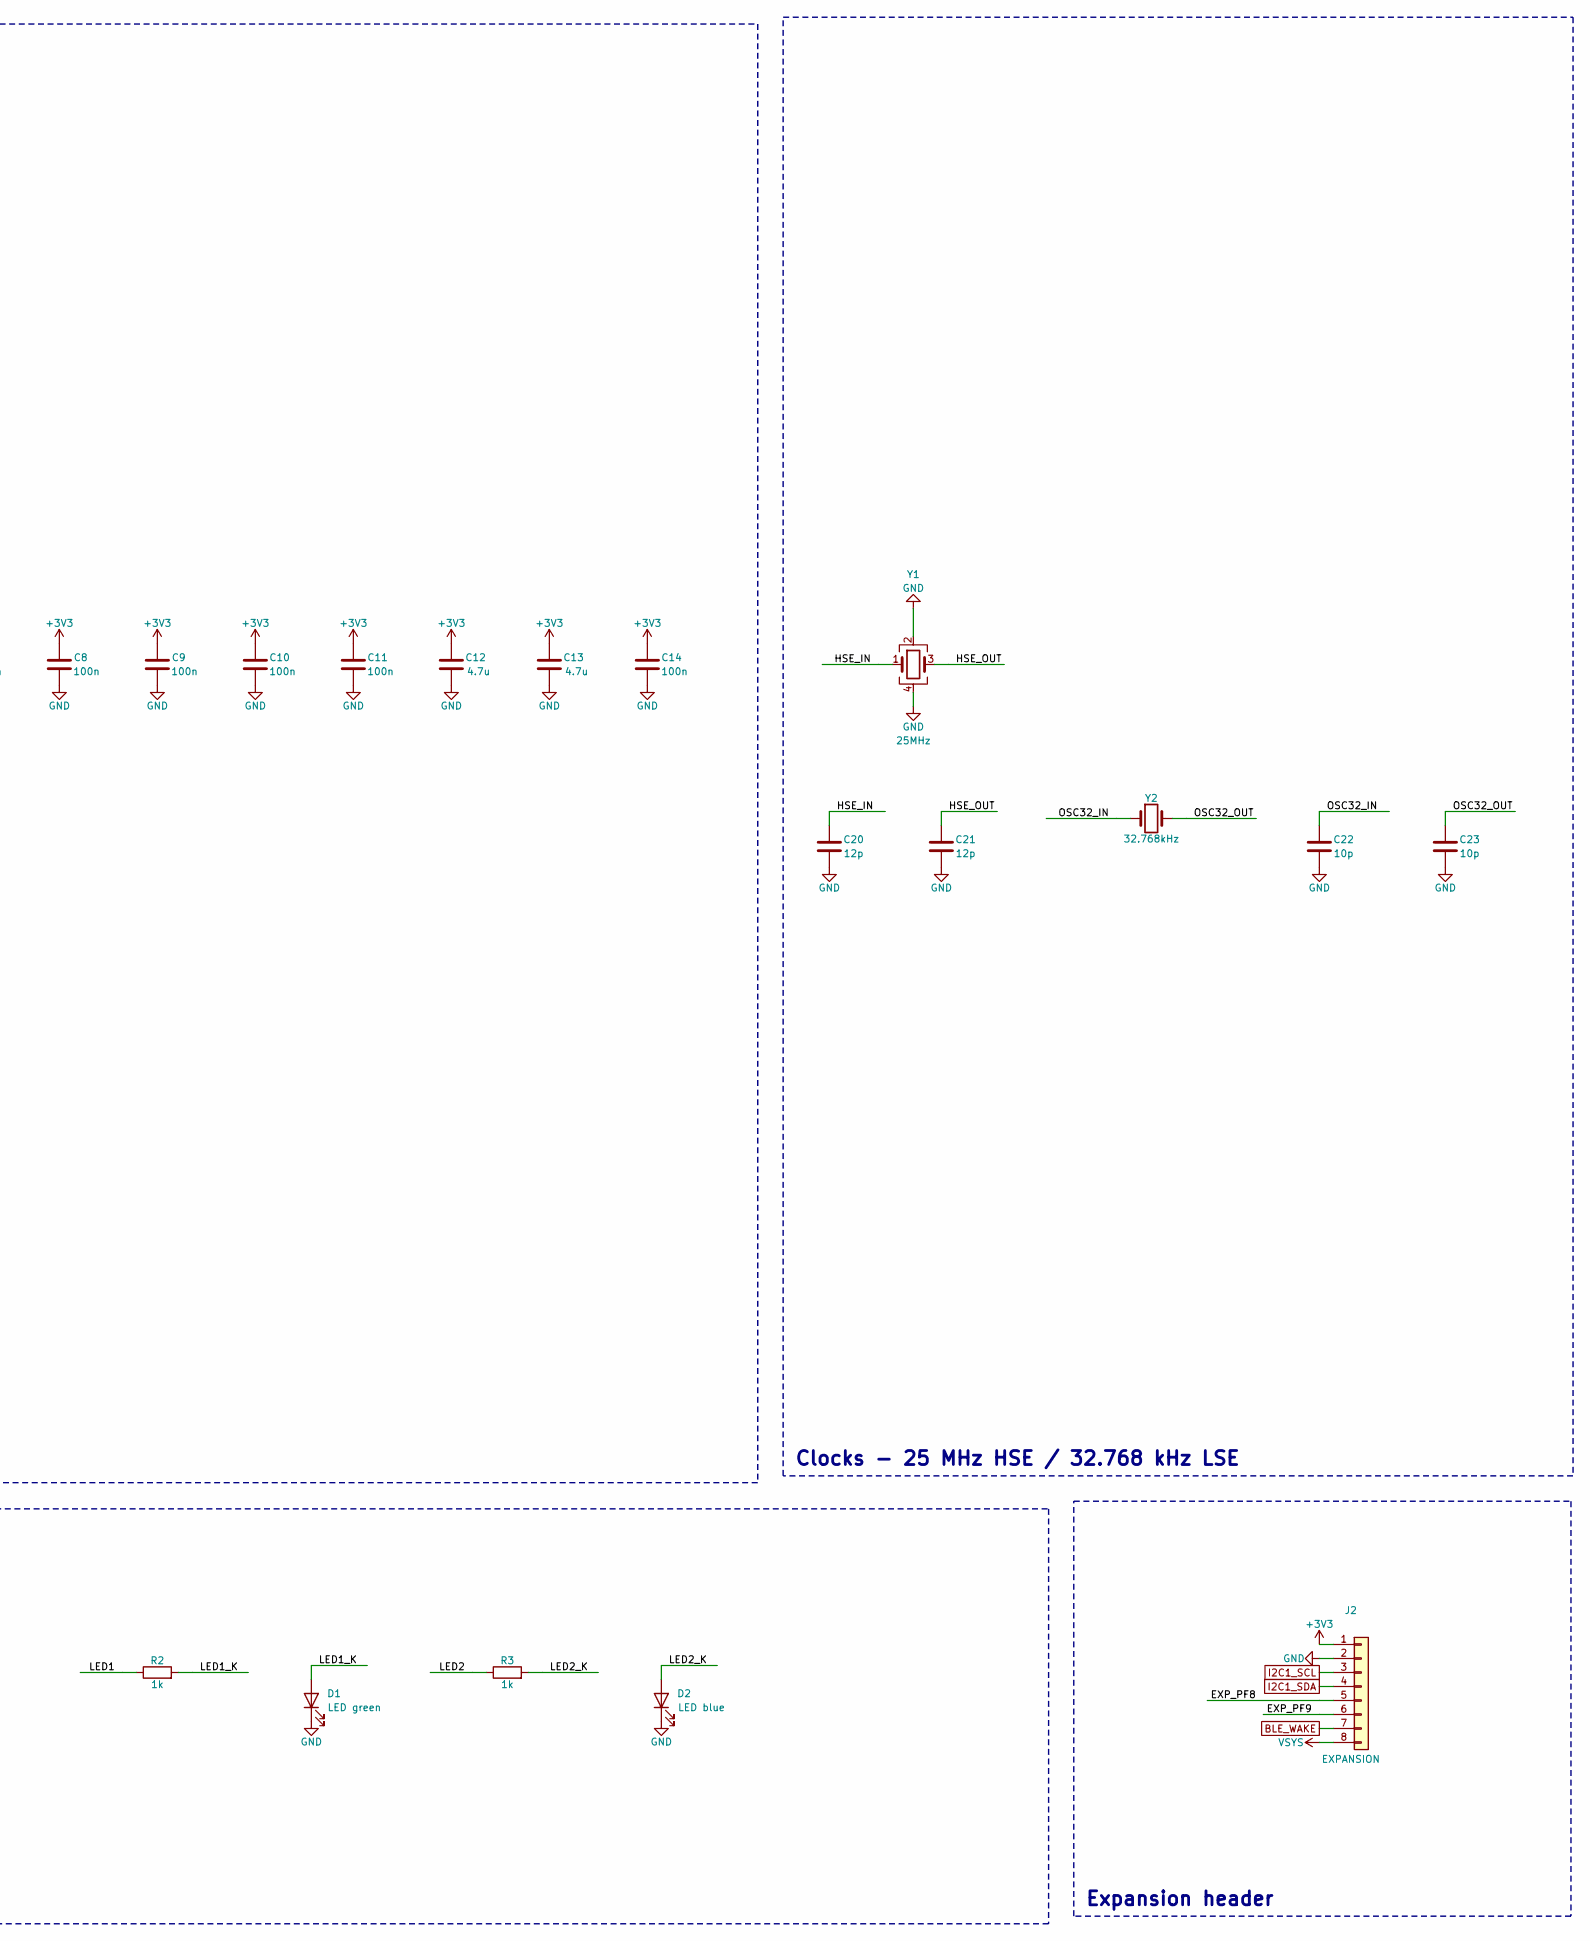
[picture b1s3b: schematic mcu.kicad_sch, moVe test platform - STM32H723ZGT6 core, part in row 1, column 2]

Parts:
C1, C2, C3, C4, C5, C6, C7, C8, C9, C10, C11, C14, C16, C17, C24: 100n; C_0603_1608Metric
C12, C13: 4.7u; C_0805_2012Metric
C15: 1u; C_0603_1608Metric
C18, C19: 2.2u; C_0603_1608Metric
C20, C21: 12p; C_0603_1608Metric
C22, C23: 10p; C_0603_1608Metric
D1: LED green; LED_0603_1608Metric
D2: LED blue; LED_0603_1608Metric
FB1: 600R@100MHz; L_0603_1608Metric; MPN BLM18PG601SN1D
J1: SWD; PinHeader_2x05_P1.27mm_Vertical_SMD; MPN FTSH-105-01-L-DV-K-P
J2: EXPANSION; PinHeader_1x08_P2.54mm_Vertical
R1: 10k; R_0603_1608Metric
R2, R3: 1k; R_0603_1608Metric
SW1: RESET; SW_SPST_PTS645; MPN PTS645SK43SMTR92 LFS
SW2: BOOT0; SW_SPST_PTS645; MPN PTS645SK43SMTR92 LFS
U1: STM32H723ZGT6; LQFP-144_20x20mm_P0.5mm; MPN STM32H723ZGT6
Y1: 25MHz; Crystal_SMD_3225-4Pin_3.2x2.5mm; MPN ABM8-25.000MHZ-B2-T (CL=10pF)
Y2: 32.768kHz; Crystal_SMD_3215-2Pin_3.2x1.5mm; MPN ABS07-32.768KHZ-7-T (CL=7pF)

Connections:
+3V3: C1.1, C2.1, C3.1, C4.1, C5.1, C6.1, C7.1, C8.1, C9.1, C10.1, C11.1, C12.1, C13.1, C14.1, FB1.1, J1.1 (VTref), J2.1, SW2.1, U1.6 (VBAT), U1.17 (VDD), U1.30 (VDD), U1.39 (VDD), U1.52 (VDD), U1.62 (VDD), U1.72 (VDD), U1.84 (VDD), U1.95 (VDD33USB), U1.108 (VDD), U1.121 (VDD), U1.131 (VDD), U1.143 (PDR_ON), U1.144 (VDD); also elsewhere on the board
/MCU/BOOT0: R1.1, SW2.2, U1.138 (BOOT0)
/MCU/EXP_PF8: J2.5, U1.20 (PF8)
/MCU/EXP_PF9: J2.6, U1.21 (PF9)
/MCU/HSE_IN: C20.1, U1.23 (PH0), Y1.1
/MCU/HSE_OUT: C21.1, U1.24 (PH1), Y1.3
/MCU/LED1: R2.1, U1.18 (PF6)
/MCU/LED1_K: D1.2 (A), R2.2
/MCU/LED2: R3.1, U1.19 (PF7)
/MCU/LED2_K: D2.2 (A), R3.2
/MCU/NRST: C24.1, J1.10 (~RESET), SW1.1, U1.25 (NRST)
/MCU/OSC32_IN: C22.1, U1.8 (PC14), Y2.1
/MCU/OSC32_OUT: C23.1, U1.9 (PC15), Y2.2
/MCU/SWCLK: J1.4 (SWCLK/TCK), U1.109 (PA14(JTCK)
/MCU/SWDIO: J1.2 (SWDIO/TMS), U1.105 (PA13(JTMS)
/MCU/SWO: J1.6 (SWO/TDO), U1.133 (PB3(JTDO)
BARO_INT: U1.134 (PB4(NJTRST)); also elsewhere on the board
BLE_CTS: U1.80 (PD11); also elsewhere on the board
BLE_RESET_N: U1.82 (PD13); also elsewhere on the board
BLE_RTS: U1.81 (PD12); also elsewhere on the board
BLE_SW1: U1.118 (PD4); also elsewhere on the board
BLE_SW2: U1.119 (PD5); also elsewhere on the board
BLE_UART_RX: U1.70 (PB11); also elsewhere on the board
BLE_UART_TX: U1.111 (PC10); also elsewhere on the board
BLE_WAKE: J2.7, U1.113 (PC12); also elsewhere on the board
BL_PWM: U1.139 (PB8); also elsewhere on the board
FMC_A0: U1.10 (PF0); also elsewhere on the board
FMC_A1: U1.11 (PF1); also elsewhere on the board
FMC_A2: U1.12 (PF2); also elsewhere on the board
FMC_A3: U1.13 (PF3); also elsewhere on the board
FMC_A4: U1.14 (PF4); also elsewhere on the board
FMC_A5: U1.15 (PF5); also elsewhere on the board
FMC_A6: U1.50 (PF12); also elsewhere on the board
FMC_A7: U1.53 (PF13); also elsewhere on the board
FMC_A8: U1.54 (PF14); also elsewhere on the board
FMC_A9: U1.55 (PF15); also elsewhere on the board
FMC_A10: U1.56 (PG0); also elsewhere on the board
FMC_A11: U1.57 (PG1); also elsewhere on the board
FMC_A12: U1.87 (PG2); also elsewhere on the board
FMC_BA0: U1.89 (PG4); also elsewhere on the board
FMC_BA1: U1.90 (PG5); also elsewhere on the board
FMC_D0: U1.85 (PD14); also elsewhere on the board
FMC_D1: U1.86 (PD15); also elsewhere on the board
FMC_D2: U1.114 (PD0); also elsewhere on the board
FMC_D3: U1.115 (PD1); also elsewhere on the board
FMC_D4: U1.58 (PE7); also elsewhere on the board
FMC_D5: U1.59 (PE8); also elsewhere on the board
FMC_D6: U1.60 (PE9); also elsewhere on the board
FMC_D7: U1.63 (PE10); also elsewhere on the board
FMC_D8: U1.64 (PE11); also elsewhere on the board
FMC_D9: U1.65 (PE12); also elsewhere on the board
FMC_D10: U1.66 (PE13); also elsewhere on the board
FMC_D11: U1.67 (PE14); also elsewhere on the board
FMC_D12: U1.68 (PE15); also elsewhere on the board
FMC_D13: U1.77 (PD8); also elsewhere on the board
FMC_D14: U1.78 (PD9); also elsewhere on the board
FMC_D15: U1.79 (PD10); also elsewhere on the board
FMC_NBL0: U1.141 (PE0); also elsewhere on the board
FMC_NBL1: U1.142 (PE1); also elsewhere on the board
FMC_SDCKE0: U1.29 (PC3_C); also elsewhere on the board
FMC_SDCLK: U1.93 (PG8); also elsewhere on the board
FMC_SDNCAS: U1.132 (PG15); also elsewhere on the board
FMC_SDNE0: U1.28 (PC2_C); also elsewhere on the board
FMC_SDNRAS: U1.49 (PF11); also elsewhere on the board
FMC_SDNWE: U1.43 (PA7); also elsewhere on the board
GND: C1.2, C2.2, C3.2, C4.2, C5.2, C6.2, C7.2, C8.2, C9.2, C10.2, C11.2, C12.2, C13.2, C14.2, C15.2, C16.2, C17.2, C18.2, C19.2, C20.2, C21.2, C22.2, C23.2, C24.2, D1.1 (K), D2.1 (K), J1.3 (GND), J1.5 (GND), J1.9 (GNDDetect), J2.2, R1.2, SW1.2, U1.16 (VSS), U1.31 (VSSA), U1.38 (VSS), U1.51 (VSS), U1.61 (VSS), U1.83 (VSS), U1.94 (VSS), U1.107 (VSS), U1.120 (VSS), U1.130 (VSS), Y1.2, Y1.4; also elsewhere on the board
GPS_EXTINT: U1.129 (PG14); also elsewhere on the board
GPS_RESET_N: U1.88 (PG3); also elsewhere on the board
GPS_TIMEPULSE: U1.1 (PE2); also elsewhere on the board
GPS_UART_RX: U1.76 (PB15); also elsewhere on the board
GPS_UART_TX: U1.75 (PB14); also elsewhere on the board
I2C1_SCL: J2.3, U1.136 (PB6); also elsewhere on the board
I2C1_SDA: J2.4, U1.137 (PB7); also elsewhere on the board
IMU_INT: U1.2 (PE3); also elsewhere on the board
LCD_STBYB: U1.74 (PB13); also elsewhere on the board
LTDC_B0: U1.3 (PE4); also elsewhere on the board
LTDC_B1: U1.102 (PA10); also elsewhere on the board
LTDC_B2: U1.37 (PA3); also elsewhere on the board
LTDC_B3: U1.100 (PA8); also elsewhere on the board
LTDC_B4: U1.112 (PC11); also elsewhere on the board
LTDC_B5: U1.135 (PB5); also elsewhere on the board
LTDC_B6: U1.110 (PA15(JTDI)); also elsewhere on the board
LTDC_B7: U1.116 (PD2); also elsewhere on the board
LTDC_CLK: U1.92 (PG7); also elsewhere on the board
LTDC_DE: U1.22 (PF10); also elsewhere on the board
LTDC_G0: U1.4 (PE5); also elsewhere on the board
LTDC_G1: U1.5 (PE6); also elsewhere on the board
LTDC_G2: U1.42 (PA6); also elsewhere on the board
LTDC_G3: U1.99 (PC9); also elsewhere on the board
LTDC_G4: U1.69 (PB10); also elsewhere on the board
LTDC_G5: U1.27 (PC1); also elsewhere on the board
LTDC_G6: U1.97 (PC7); also elsewhere on the board
LTDC_G7: U1.117 (PD3); also elsewhere on the board
LTDC_HSYNC: U1.96 (PC6); also elsewhere on the board
LTDC_R0: U1.128 (PG13); also elsewhere on the board
LTDC_R1: U1.36 (PA2); also elsewhere on the board
LTDC_R2: U1.35 (PA1); also elsewhere on the board
LTDC_R3: U1.46 (PB0); also elsewhere on the board
LTDC_R4: U1.41 (PA5); also elsewhere on the board
LTDC_R5: U1.26 (PC0); also elsewhere on the board
LTDC_R6: U1.47 (PB1); also elsewhere on the board
LTDC_R7: U1.91 (PG6); also elsewhere on the board
LTDC_VSYNC: U1.40 (PA4); also elsewhere on the board
MQ7_ADC: U1.45 (PC5); also elsewhere on the board
MQ7_HEAT: U1.140 (PB9); also elsewhere on the board
SDMMC2_CK: U1.122 (PD6); also elsewhere on the board
SDMMC2_CMD: U1.34 (PA0); also elsewhere on the board
SDMMC2_D0: U1.124 (PG9); also elsewhere on the board
SDMMC2_D1: U1.125 (PG10); also elsewhere on the board
SDMMC2_D2: U1.126 (PG11); also elsewhere on the board
SDMMC2_D3: U1.127 (PG12); also elsewhere on the board
SD_DETECT: U1.98 (PC8); also elsewhere on the board
TOUCH_INT_N: U1.7 (PC13); also elsewhere on the board
TOUCH_RST_N: U1.73 (PB12); also elsewhere on the board
USB_DM: U1.103 (PA11); also elsewhere on the board
USB_DP: U1.104 (PA12); also elsewhere on the board
VBAT_SENSE: U1.44 (PC4); also elsewhere on the board
VBUS_SENSE: U1.101 (PA9); also elsewhere on the board
VCAP: C18.1, C19.1, U1.71 (VCAP), U1.106 (VCAP)
VDDA: C15.1, C16.1, C17.1, FB1.2, U1.32 (VREF+), U1.33 (VDDA)
VSYS: J2.8; also elsewhere on the board

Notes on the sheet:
STM32H723ZGT6
Supply decoupling
Clocks - 25 MHz HSE / 32.768 kHz LSE
Reset and boot
SWD debug
Status LEDs
Expansion header
